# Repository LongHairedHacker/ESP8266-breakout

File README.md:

ESP8266 Breakout Chaos InKL Version
===================================

Slightly modified version of limpkins ESP8266 breakout board.
See: http://www.limpkin.fr/index.php?post/2014/11/27/A-Development-Board-for-the-ESP8266-03 for the original files.

Licenses
--------
Anything in the folder libs/smisitoto_eu/ is taken from http://smisioto.no-ip.org/elettronica/kicad/kicad-en.htm The files are made avaible under the Creative Commons license rev2.5 Attribution-ShareAlike. (see https://creativecommons.org/licenses/by-sa/2.5/)

The Chaos InKL logo is licensed CC BY-NC-SA 3.0.

The exploding open hardware logo (artwork/hacker_logo.mod) is my private logo,
you are not allowed to use it on your own design and you should therefore remove it,
after forking this repository.

All remaining files repository are under the CERN Open Hardware Licence v1.2.

Thanks to limpkin for the initial design.

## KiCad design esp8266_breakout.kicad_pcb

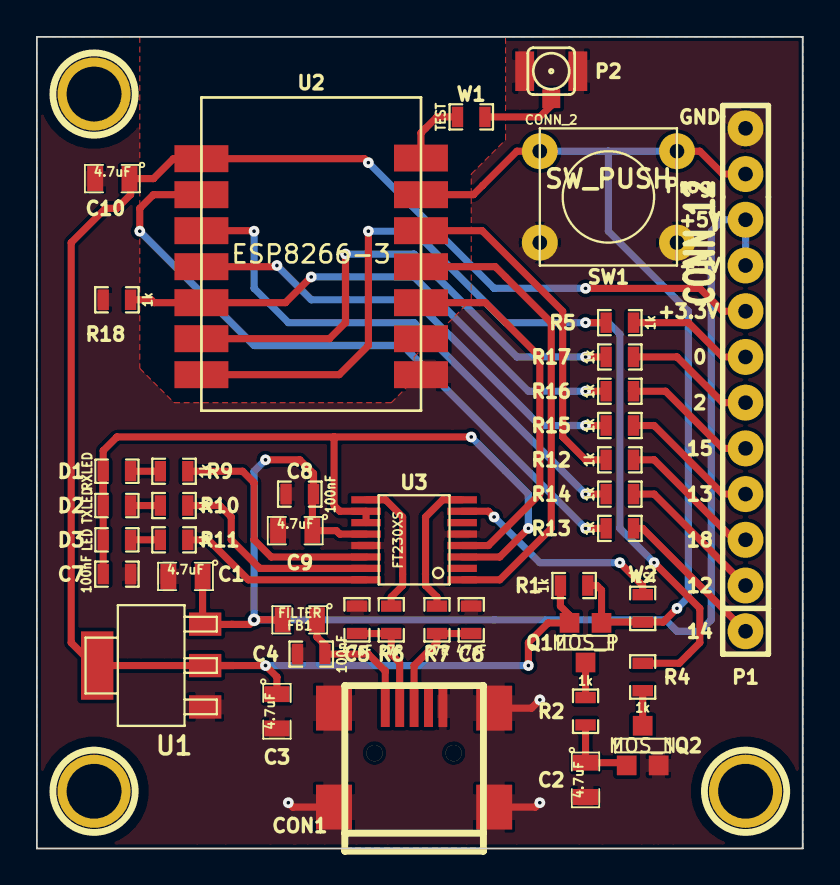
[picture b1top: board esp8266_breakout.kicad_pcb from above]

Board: 2 copper layers, 42.5 x 45.1 mm, 44 parts (0 on the bottom side), 38 nets.

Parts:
1PIN, 1PIN#2, 1PIN#3: P***; 1pin
C1, C2, C3, C9, C10: 4.7uF; SM0805
C4, C7, C8: 100nF; SM0603_Resistor
C5, C6: 47pF; SM0603_Resistor
CON1: USB-MICRO-B2; USB_MINI_B
D1: RXLED; SM0603_Capa
D2: TXLED; SM0603_Capa
D3: LED; SM0603_Capa
FB1: FILTER; SM0805
P1: CONN_12; SIL-12
P2: CONN_2; coaxial_u.fl-r-smt-1
Q1: MOS_P; SOT23GDS_L
Q2: MOS_N; SOT23GDS_L
R1, R2, R4, R5, R9, R10, R11, R12, R13, R14, R15, R16, R17, R18: 1k; SM0603_Resistor
R6, R7: 27R; SM0603_Resistor
SW1: SW_PUSH; SW_PUSH_SMALL
U1: NCP1117LP; sot223
U2: ESP8266-3
U3: FT230XS; ssop-16
W1, W2: TEST; SM0603_Resistor

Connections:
+3.3V: C3.1, C10.1, P1.8, Q1.S, R1.1, U1.2, U1.4, U2.8
CON_GPIO0: P1.7, R5.1
CON_GPIO2: P1.6, R17.2
CON_GPIO12: P1.2, R14.2
CON_GPIO13: P1.4, R15.2
CON_GPIO14: P1.1, R13.2
CON_GPIO15: P1.5, R16.2
CON_GPIO18: P1.3, R12.2
FT230_RX: U2.3, U3.4
FT230_TX: U2.4, U3.1
GND: C1.2, C2.2, C3.2, C4.2, C5.2, C6.2, C7.2, C8.2, C9.2, C10.2, CON1.5, CON1.6, CON1.7, CON1.8, CON1.9, P1.12, P2.2, Q2.S, R18.2, SW1.1, U1.1, U2.1, U3.5, U3.13
GPIO0: R4.2, R5.2, U2.14
unnamed: C5.1, CON1.2, R6.1
unnamed: C6.1, CON1.3, R7.1
unnamed: R7.2, U3.8
unnamed: R6.2, U3.9
unnamed: R17.1, U2.13
unnamed: C7.1, D1.1, D2.1, D3.1, U3.3, U3.10, U3.11
unnamed: D3.2, R11.2
unnamed: D1.2, R9.2
unnamed: Q2.D, R4.1
unnamed: C2.1, Q2.G, R2.2
unnamed: Q1.D, R2.1
unnamed: U2.7, W1.1
unnamed: U3.7, W2.1
unnamed: R11.1, U3.16
unnamed: R9.1, U3.14
unnamed: R10.1, U3.15
unnamed: P2.1, W1.2
unnamed: D2.2, R10.2
unnamed: R14.1, U2.10
unnamed: R12.1, U2.5
unnamed: R13.1, U2.9
unnamed: R15.1, U2.11
unnamed: R16.1, R18.1, U2.12
PROG_SW: P1.11, Q1.G, R1.2, SW1.2, U2.6, W2.2
VCC: C1.1, C8.1, C9.1, FB1.2, P1.9, P1.10, U1.3, U3.12
VDD: C4.1, CON1.1, FB1.1

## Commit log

2014-12-02 Starting reworking for ordering pcbs
2014-12-02 Finished first reworked layout version
2014-12-02 Added ufl connector cleaned up schematic
2014-12-04 Added logos and fancy silkscreen
2014-12-04 Added proper licensing
2014-12-04 Added .gitignore Generated postscript
2014-12-04 Added version and github url
2014-12-05 Removed french layer names ... because they were french
2014-12-09 Fixed footprints
2014-12-12 Final adjustments for Version 1.0 Generated gerbers
2016-02-17 Added PDF
